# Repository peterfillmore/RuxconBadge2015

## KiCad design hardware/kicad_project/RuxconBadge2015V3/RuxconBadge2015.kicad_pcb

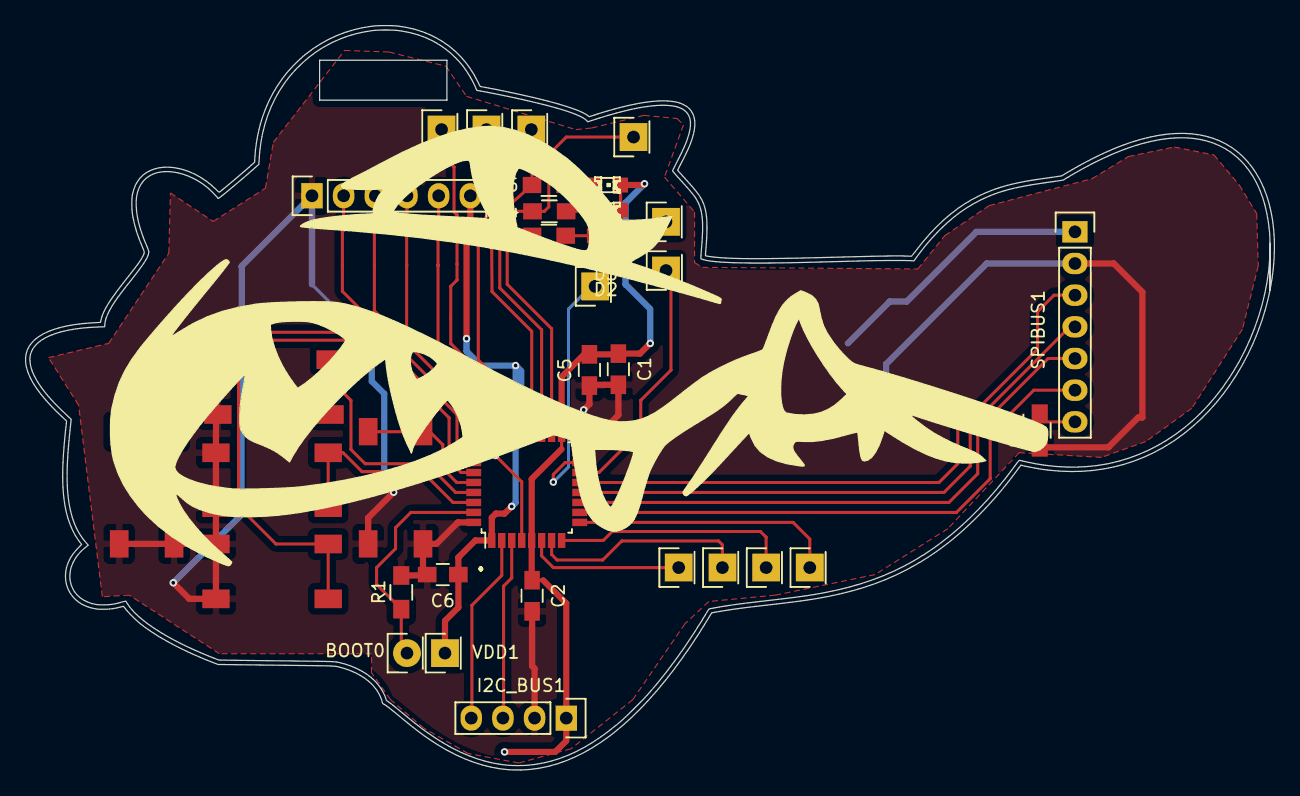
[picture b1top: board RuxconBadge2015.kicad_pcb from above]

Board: 2 copper layers, 100.2 x 59.7 mm, 35 parts (1 on the bottom side), 33 nets.

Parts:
BOOT0: CONN_01X01; Socket_Strip_Straight_1x01
BT1: BU2032-SM; BCM2032-SM
C1: 1uF; C_0805_HandSoldering
C2, C5, C6: 100nF; C_0805_HandSoldering
D2: GREEN; LED-0805
D3: RED; LED-0805
D4: YELLOW; LED-0805
I2C_BUS1: CONN_01X04; Pin_Header_Straight_1x04
P6: CONN_01X06; Socket_Strip_Straight_1x06
PA0_ADC_IN0, PA1_ADCIN1, PA2_USART1TX1, PA3_USART1RX1, PA8_GREEN1, PA9_RED1, PA10_YELLOW1, PA11, PA12: CONN_01X01; Socket_Strip_Straight_1x01
PB0_I2C1SCL1, PB1_I2C1SDA1: CONN_01X01; Socket_Strip_Straight_1x01
R1, R12: 100k; R_0805_HandSoldering
R13, R14, R15: 470; R_0805_HandSoldering
SPIBUS1: CONN_01X07; Pin_Header_Straight_1x07
SW_DOWN1: Switch_DPST; SW_SPST_TL3301
SW_ENTER1: Switch_DPST; SW_SPST_TL3301
SW_LEFT1: Switch_DPST; SW_SPST_TL3301
SW_RIGHT1: Switch_DPST; SW_SPST_TL3301
SW_UP1: Switch_DPST; SW_SPST_TL3301
U3: STM32F030K6T6; LQFP-32_7x7mm_Pitch0.8mm
VDD1: VDD; Socket_Strip_Straight_1x01

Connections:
BOOT0: BOOT0.1, R1.2, U3.31
GND: BT1.2, C1.2, C2.2, C5.2, C6.2, I2C_BUS1.2, P6.1, R1.1, R12.2, SPIBUS1.2, SW_DOWN1.1, SW_DOWN1.3, SW_ENTER1.1, SW_ENTER1.3, SW_LEFT1.1, SW_LEFT1.3, SW_RIGHT1.1, SW_RIGHT1.3, SW_UP1.1, SW_UP1.3, U3.16, U3.32
unnamed: D2.2, R13.2
unnamed: D3.2, R14.2
unnamed: D4.2, R15.2
unnamed: R12.1, SPIBUS1.7
PA0: PA0_ADC_IN0.1, U3.6
PA1: PA1_ADCIN1.1, U3.7
PA2: PA2_USART1TX1.1, U3.8
PA3: PA3_USART1RX1.1, U3.9
PA4: SPIBUS1.6, U3.10
PA5: SPIBUS1.5, U3.11
PA6: SPIBUS1.4, U3.12
PA8: PA8_GREEN1.1, R13.1, U3.18
PA9: PA9_RED1.1, R14.1, U3.19
PA10: PA10_YELLOW1.1, R15.1, U3.20
PA11: PA11.1, U3.21
PA12: PA12.1, U3.22
PA13: P6.5, U3.23
PB0: PB0_I2C1SCL1.1, U3.14
PB1: PB1_I2C1SDA1.1, U3.15
PB3: SW_LEFT1.2, SW_LEFT1.4, U3.26
PB4: SW_DOWN1.2, SW_DOWN1.4, U3.27
PB5: SW_RIGHT1.2, SW_RIGHT1.4, U3.28
PB6: SW_UP1.2, SW_UP1.4, U3.29
PB7: SW_ENTER1.2, SW_ENTER1.4, U3.30
PF0: I2C_BUS1.4, U3.2
PF1: I2C_BUS1.3, U3.3
SPI1_MOSI: SPIBUS1.3, U3.13
SWDIO: P6.4, U3.24
USART1_RX: P6.2, U3.25
VDD: BT1.1, C1.1, C2.1, C5.1, C6.1, D2.1, D3.1, D4.1, I2C_BUS1.1, P6.6, SPIBUS1.1, U3.1, U3.5, U3.17, VDD1.1
nRESET: P6.3, U3.4

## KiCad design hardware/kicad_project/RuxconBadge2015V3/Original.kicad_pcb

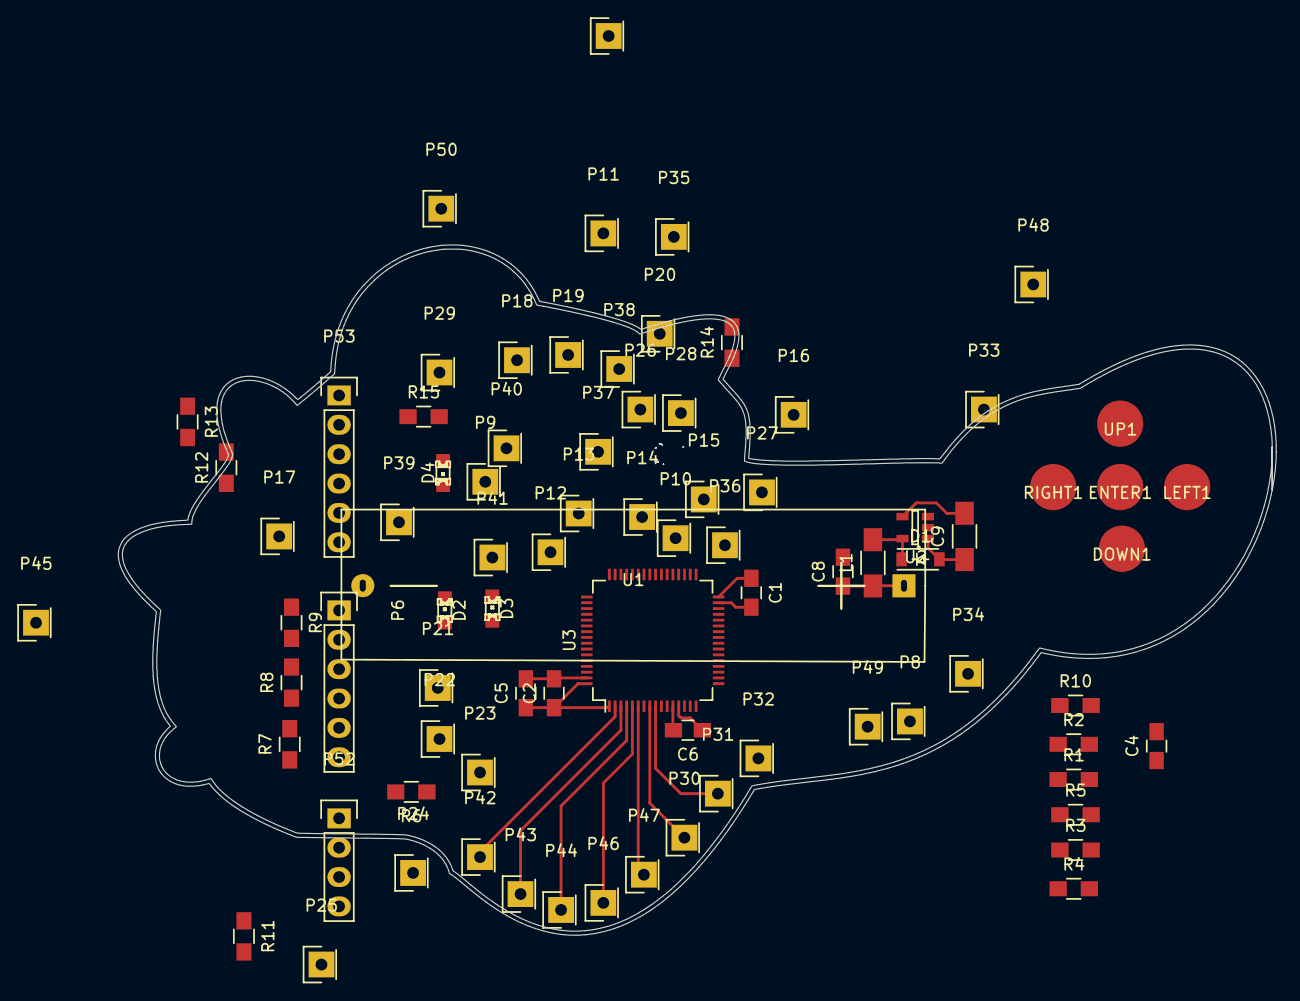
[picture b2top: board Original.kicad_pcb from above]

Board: 2 copper layers, 100.2 x 59.7 mm, 82 parts (0 on the bottom side), 72 nets.

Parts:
C1: 1uF; C_0805_HandSoldering
C2, C5, C6: 100nF; C_0805_HandSoldering
C4: 22nF; C_0805_HandSoldering
C8: 10uF; C_0805_HandSoldering
C9: 68uF; C_1206_HandSoldering
D1: D_Schottky_Small; SOD-123
D2: GREEN; LED-0805
D3: RED; LED-0805
D4: YELLOW; LED-0805
DOWN1: CONN_01X01; PCB_Touch_Button
ENTER1: CONN_01X01; PCB_Touch_Button
L1: 47uH; C_1206_HandSoldering
LEFT1: CONN_01X01; PCB_Touch_Button
P6: CONN_01X06; Socket_Strip_Straight_1x06
P8, P9, P10, P11, P12, P13, P14, P15, P16, P17, P18, P19, P20, P21, P22, P23, P24, P25, P26, P27, P28, P29, P30, P31, P32, P33, P34, P35, P36, P37, P38, P39, P40, P41, P42, P43, P44, P45, P46, P47, P48, P49, P50, P51: CONN_01X01; Socket_Strip_Straight_1x01
P52: CONN_01X04; Pin_Header_Straight_1x04
P53: CONN_01X06; Pin_Header_Straight_1x06
R1, R2, R3, R4, R5: 10k; R_0805_HandSoldering
R6, R7, R8, R9: 22; R_0805_HandSoldering
R10: 1k; R_0805_HandSoldering
R11: 510; R_0805_HandSoldering
R12: R; R_0805_HandSoldering
R13, R14, R15: 470; R_0805_HandSoldering
RIGHT1: CONN_01X01; PCB_Touch_Button
U1: BCAAAPC; BCAAAPC footprint
U2: NCP1402; SOT-23-5
U3: STM32F051RX; LQFP-64_10x10mm_Pitch0.5mm
UP1: CONN_01X01; PCB_Touch_Button

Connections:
BOOT0: R11.2, U3.60
GND: C1.2, C2.2, C4.2, C5.2, C6.2, C8.2, C9.2, P6.1, P52.2, P53.2, R11.1, R12.2, U1.2, U2.4, U3.12, U3.31, U3.63
I2C1_SDA: P25.1, P52.4, U3.30
unnamed: C8.1, L1.1, U1.1
unnamed: D1.1, L1.2, U2.5
unnamed: D2.2, R13.2
unnamed: D3.2, R14.2
unnamed: D4.2, R15.2
unnamed: DOWN1.1, R3.2
unnamed: ENTER1.1, R5.2
unnamed: LEFT1.1, R4.2
unnamed: P6.2, R9.2
unnamed: P6.3, R8.2
unnamed: P6.4, R7.2
unnamed: P6.5, R6.2
unnamed: P53.6, R12.1
unnamed: R1.2, UP1.1
unnamed: R2.2, RIGHT1.1
PA5: P8.1, R13.1, U3.21
PA8: P9.1, R14.1, U3.41
PA9: P10.1, R15.1, U3.42
PA10: P11.1, U3.43
PA11: P12.1, U3.44
PA12: P13.1, U3.45
PB1: P15.1, U3.27
PB2: P16.1, U3.28
PB3: P17.1, U3.55
PB4: P18.1, U3.56
PB5: P19.1, U3.57
PB6: P20.1, U3.58
PB7: P21.1, U3.59
PB8: P22.1, U3.61
PB9: P23.1, U3.62
PB10: P24.1, P52.3, U3.29
PB13: P27.1, P53.3, U3.34
PC0: P30.1, U3.8
PC1: P31.1, U3.9
PC2: P32.1, U3.10
PC3: P33.1, U3.11
PC4: P34.1, U3.24
PC6: P35.1, U3.37
PC7: P36.1, U3.38
PC8: P37.1, U3.39
PC9: P38.1, U3.40
PC10: P39.1, U3.51
PC11: P40.1, U3.52
PC12: P41.1, U3.53
PC13: P42.1, U3.2
PC14: P43.1, U3.3
PC15: P44.1, U3.4
PD2: P45.1, U3.54
PF0: P46.1, U3.5
PF1: P47.1, U3.6
PF4: P48.1, U3.18
PF5: P49.1, U3.19
PF6: P50.1, U3.47
PF7: P51.1, U3.48
SHIELD: R10.1, U3.25
SPI1_MISO: P28.1, U3.35
SPI1_MOSI: P29.1, P53.4, U3.36
SPI1_NSS: P26.1, P53.5, U3.33
SWCLK: R6.1, U3.49
SWDIO: P14.1, R7.1, U3.46
TS1: R1.1, U3.14
TS2: R2.1, U3.15
TS3: R3.1, U3.16
TS4: R4.1, U3.22
TS5: R5.1, U3.23
TSCT1: C4.1, U3.17
USART1_RX: R9.1, U3.50
VDD: C1.1, C2.1, C5.1, C6.1, C9.1, D1.2, D2.1, D3.1, D4.1, P6.6, P52.1, P53.1, U2.1, U2.2, U3.1, U3.13, U3.32, U3.64
nRESET: R8.1, U3.7

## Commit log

2015-09-23 inital commit
2015-09-23 added blinky project
2015-09-23 added BOM
2015-10-06 added i2c examples
2015-10-11 added more sample code
2015-10-13 updated threatbutt IoT to use funkier fonts and solved a bug in the I2C by enabling the watchdog timer. I guess i should add a TODO for that fix...
2015-10-20 added I2C timing spreadsheet
2015-10-21 added pdf of build instructions
